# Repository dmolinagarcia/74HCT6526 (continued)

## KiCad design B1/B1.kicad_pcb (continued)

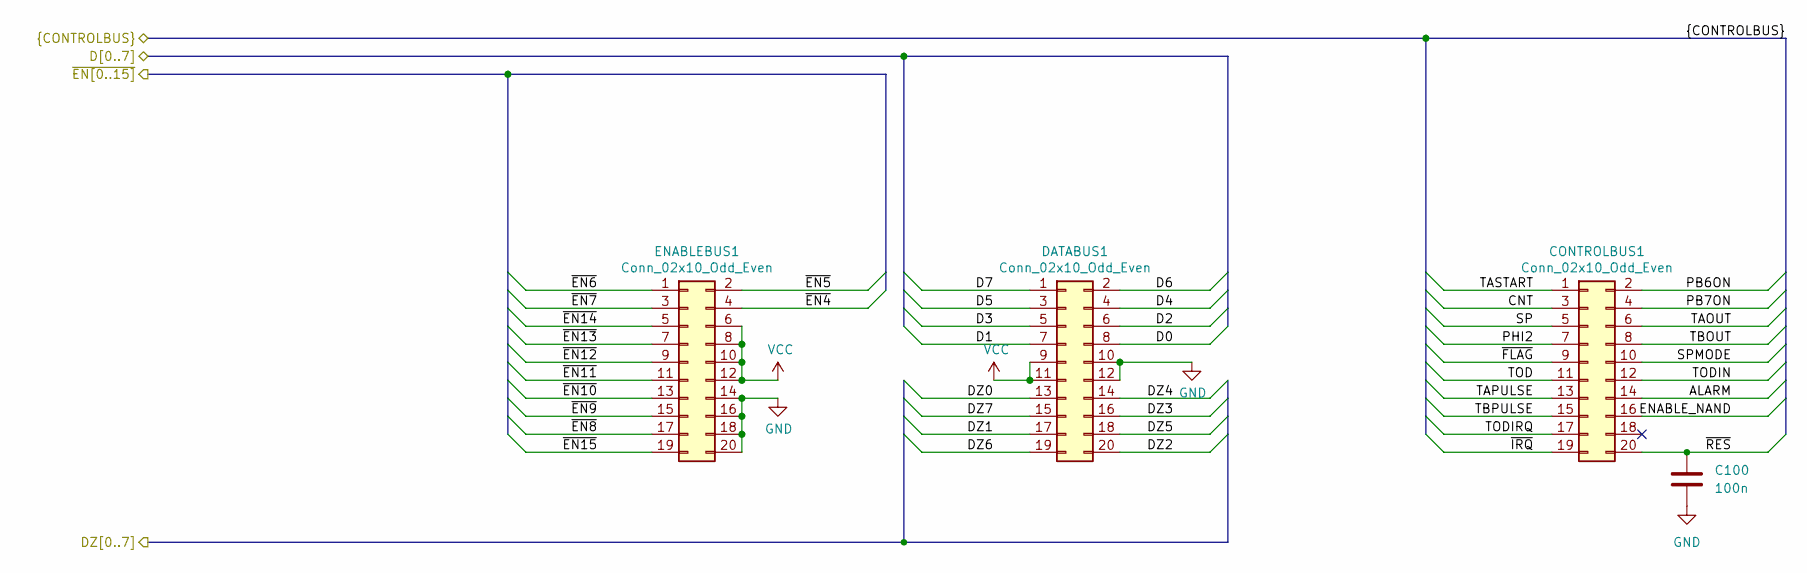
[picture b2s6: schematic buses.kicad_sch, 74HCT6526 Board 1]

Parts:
C100: 100n; C_0603_1608Metric
CONTROLBUS1: Conn_02x10_Odd_Even; PinHeader_2x10_P2.54mm_Vertical
DATABUS1: Conn_02x10_Odd_Even; PinHeader_2x10_P2.54mm_Vertical
ENABLEBUS1: Conn_02x10_Odd_Even; PinHeader_2x10_P2.54mm_Vertical

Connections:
ALARM: CONTROLBUS1.14
CNT: CONTROLBUS1.3; also elsewhere on the board
D0: DATABUS1.8; also elsewhere on the board
D1: DATABUS1.7; also elsewhere on the board
D2: DATABUS1.6; also elsewhere on the board
D3: DATABUS1.5; also elsewhere on the board
D4: DATABUS1.4; also elsewhere on the board
D5: DATABUS1.3; also elsewhere on the board
D6: DATABUS1.2; also elsewhere on the board
D7: DATABUS1.1; also elsewhere on the board
DZ0: DATABUS1.13; also elsewhere on the board
DZ1: DATABUS1.17; also elsewhere on the board
DZ2: DATABUS1.20; also elsewhere on the board
DZ3: DATABUS1.16; also elsewhere on the board
DZ4: DATABUS1.14; also elsewhere on the board
DZ5: DATABUS1.18; also elsewhere on the board
DZ6: DATABUS1.19; also elsewhere on the board
DZ7: DATABUS1.15; also elsewhere on the board
ENABLE_NAND: CONTROLBUS1.16; also elsewhere on the board
GND: C100.2, DATABUS1.10, DATABUS1.12, ENABLEBUS1.14, ENABLEBUS1.16, ENABLEBUS1.18, ENABLEBUS1.20; also elsewhere on the board
PB6ON: CONTROLBUS1.2; also elsewhere on the board
PB7ON: CONTROLBUS1.4
PHI2: CONTROLBUS1.7; also elsewhere on the board
SP: CONTROLBUS1.5
SPMODE: CONTROLBUS1.10; also elsewhere on the board
TAOUT: CONTROLBUS1.6; also elsewhere on the board
TAPULSE: CONTROLBUS1.13; also elsewhere on the board
TASTART: CONTROLBUS1.1; also elsewhere on the board
TBOUT: CONTROLBUS1.8
TBPULSE: CONTROLBUS1.15
TOD: CONTROLBUS1.11
TODIN: CONTROLBUS1.12; also elsewhere on the board
TODIRQ: CONTROLBUS1.17
VCC: DATABUS1.9, DATABUS1.11, ENABLEBUS1.6, ENABLEBUS1.8, ENABLEBUS1.10, ENABLEBUS1.12; also elsewhere on the board
~EN4: ENABLEBUS1.4; also elsewhere on the board
~EN5: ENABLEBUS1.2; also elsewhere on the board
~EN6: ENABLEBUS1.1
~EN7: ENABLEBUS1.3
~EN8: ENABLEBUS1.17
~EN9: ENABLEBUS1.15
~EN10: ENABLEBUS1.13
~EN11: ENABLEBUS1.11
~EN12: ENABLEBUS1.9
~EN13: ENABLEBUS1.7
~EN14: ENABLEBUS1.5; also elsewhere on the board
~EN15: ENABLEBUS1.19
~FLAG: CONTROLBUS1.9
~IRQ: CONTROLBUS1.19
~RES: C100.1, CONTROLBUS1.20; also elsewhere on the board

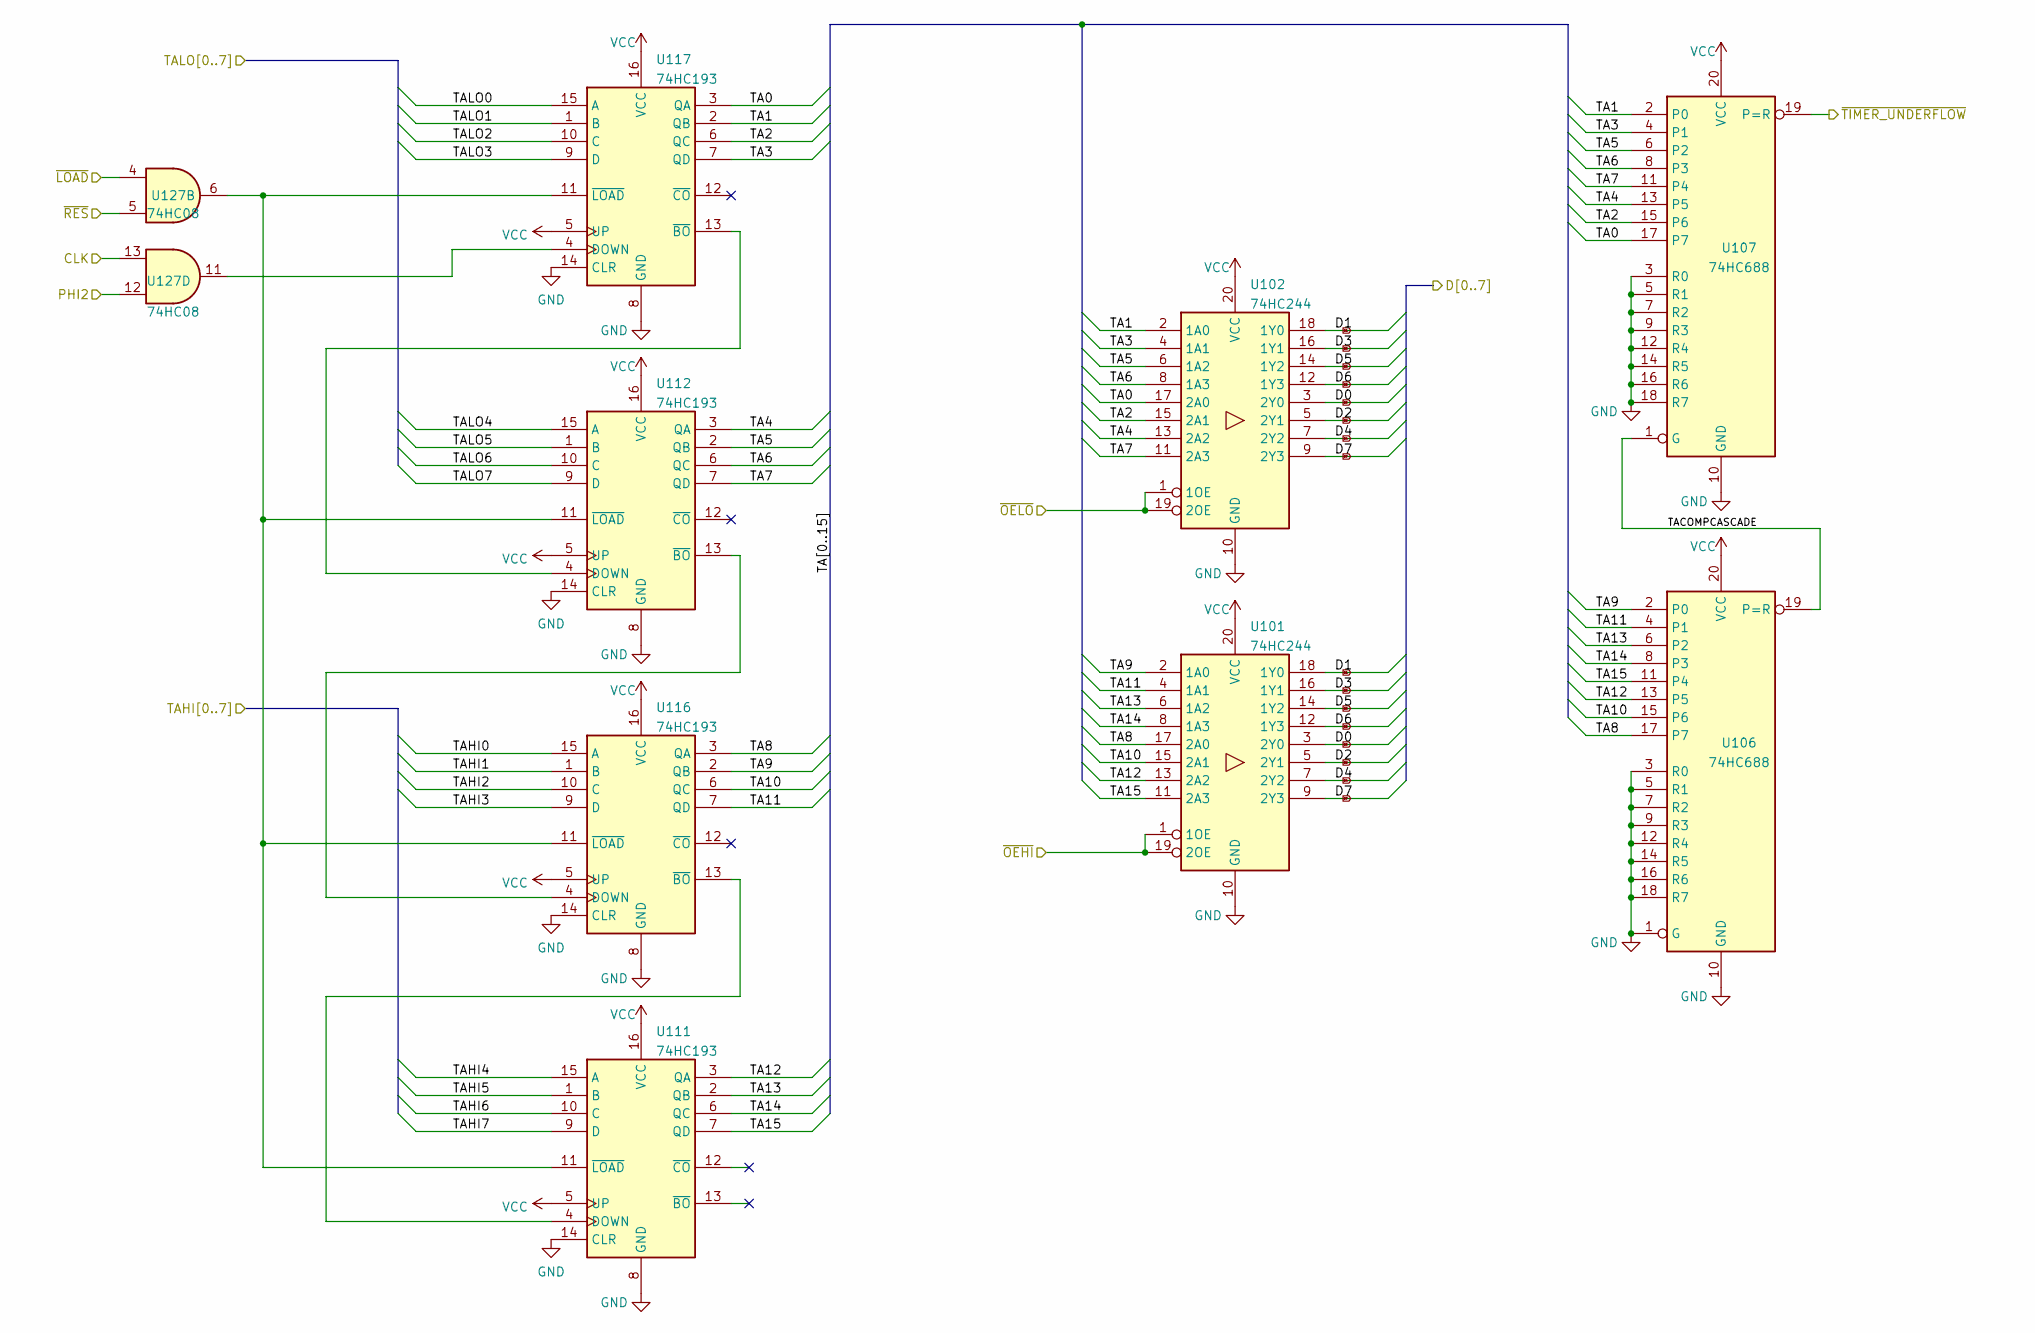
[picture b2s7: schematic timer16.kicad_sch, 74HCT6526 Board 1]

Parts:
U101, U102: 74HC244; SOIC-20W_7.5x12.8mm_P1.27mm
U106, U107: 74HC688; SOIC-20W_7.5x12.8mm_P1.27mm
U111, U112, U116, U117: 74HC193; SOIC-16_3.9x9.9mm_P1.27mm
U127: 74HC08; SO-14_3.9x8.65mm_P1.27mm

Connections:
/timera/TACOUNT: U127.13; also elsewhere on the board
/timera/timer16/TA0: U102.17 (2A0), U107.17 (P7), U117.3 (QA)
/timera/timer16/TA1: U102.2 (1A0), U107.2 (P0), U117.2 (QB)
/timera/timer16/TA2: U102.15 (2A1), U107.15 (P6), U117.6 (QC)
/timera/timer16/TA3: U102.4 (1A1), U107.4 (P1), U117.7 (QD)
/timera/timer16/TA4: U102.13 (2A2), U107.13 (P5), U112.3 (QA)
/timera/timer16/TA5: U102.6 (1A2), U107.6 (P2), U112.2 (QB)
/timera/timer16/TA6: U102.8 (1A3), U107.8 (P3), U112.6 (QC)
/timera/timer16/TA7: U102.11 (2A3), U107.11 (P4), U112.7 (QD)
/timera/timer16/TA8: U101.17 (2A0), U106.17 (P7), U116.3 (QA)
/timera/timer16/TA9: U101.2 (1A0), U106.2 (P0), U116.2 (QB)
/timera/timer16/TA10: U101.15 (2A1), U106.15 (P6), U116.6 (QC)
/timera/timer16/TA11: U101.4 (1A1), U106.4 (P1), U116.7 (QD)
/timera/timer16/TA12: U101.13 (2A2), U106.13 (P5), U111.3 (QA)
/timera/timer16/TA13: U101.6 (1A2), U106.6 (P2), U111.2 (QB)
/timera/timer16/TA14: U101.8 (1A3), U106.8 (P3), U111.6 (QC)
/timera/timer16/TA15: U101.11 (2A3), U106.11 (P4), U111.7 (QD)
/timera/timer16/TACOMPCASCADE: U106.19 (P=R), U107.1 (G)
/timera/timer16/TAHI0: U116.15 (A); also elsewhere on the board
/timera/timer16/TAHI1: U116.1 (B); also elsewhere on the board
/timera/timer16/TAHI2: U116.10 (C); also elsewhere on the board
/timera/timer16/TAHI3: U116.9 (D); also elsewhere on the board
/timera/timer16/TAHI4: U111.15 (A); also elsewhere on the board
/timera/timer16/TAHI5: U111.1 (B); also elsewhere on the board
/timera/timer16/TAHI6: U111.10 (C); also elsewhere on the board
/timera/timer16/TAHI7: U111.9 (D); also elsewhere on the board
/timera/timer16/TALO0: U117.15 (A); also elsewhere on the board
/timera/timer16/TALO1: U117.1 (B); also elsewhere on the board
/timera/timer16/TALO2: U117.10 (C); also elsewhere on the board
/timera/timer16/TALO3: U117.9 (D); also elsewhere on the board
/timera/timer16/TALO4: U112.15 (A); also elsewhere on the board
/timera/timer16/TALO5: U112.1 (B); also elsewhere on the board
/timera/timer16/TALO6: U112.10 (C); also elsewhere on the board
/timera/timer16/TALO7: U112.9 (D); also elsewhere on the board
/timera/timer16/~TIMER_UNDERFLOW: U107.19 (P=R); also elsewhere on the board
/timera/~OETAHI: U101.1 (1OE), U101.19 (2OE); also elsewhere on the board
/timera/~OETALO: U102.1 (1OE), U102.19 (2OE); also elsewhere on the board
/timera/~TALOAD: U127.4; also elsewhere on the board
D0: U101.3 (2Y0), U102.3 (2Y0); also elsewhere on the board
D1: U101.18 (1Y0), U102.18 (1Y0); also elsewhere on the board
D2: U101.5 (2Y1), U102.5 (2Y1); also elsewhere on the board
D3: U101.16 (1Y1), U102.16 (1Y1); also elsewhere on the board
D4: U101.7 (2Y2), U102.7 (2Y2); also elsewhere on the board
D5: U101.14 (1Y2), U102.14 (1Y2); also elsewhere on the board
D6: U101.12 (1Y3), U102.12 (1Y3); also elsewhere on the board
D7: U101.9 (2Y3), U102.9 (2Y3); also elsewhere on the board
GND: U101.10 (GND), U102.10 (GND), U106.1 (G), U106.3 (R0), U106.5 (R1), U106.7 (R2), U106.9 (R3), U106.10 (GND), U106.12 (R4), U106.14 (R5), U106.16 (R6), U106.18 (R7), U107.3 (R0), U107.5 (R1), U107.7 (R2), U107.9 (R3), U107.10 (GND), U107.12 (R4), U107.14 (R5), U107.16 (R6), U107.18 (R7), U111.8 (GND), U111.14 (CLR), U112.8 (GND), U112.14 (CLR), U116.8 (GND), U116.14 (CLR), U117.8 (GND), U117.14 (CLR); also elsewhere on the board
unnamed: U111.4 (DOWN), U116.13 (~BO)
unnamed: U111.11 (~LOAD), U112.11 (~LOAD), U116.11 (~LOAD), U117.11 (~LOAD), U127.6
unnamed: U112.4 (DOWN), U117.13 (~BO)
unnamed: U112.13 (~BO), U116.4 (DOWN)
unnamed: U117.4 (DOWN), U127.11
PHI2: U127.12; also elsewhere on the board
VCC: U101.20 (VCC), U102.20 (VCC), U106.20 (VCC), U107.20 (VCC), U111.5 (UP), U111.16 (VCC), U112.5 (UP), U112.16 (VCC), U116.5 (UP), U116.16 (VCC), U117.5 (UP), U117.16 (VCC); also elsewhere on the board
~RES: U127.5; also elsewhere on the board

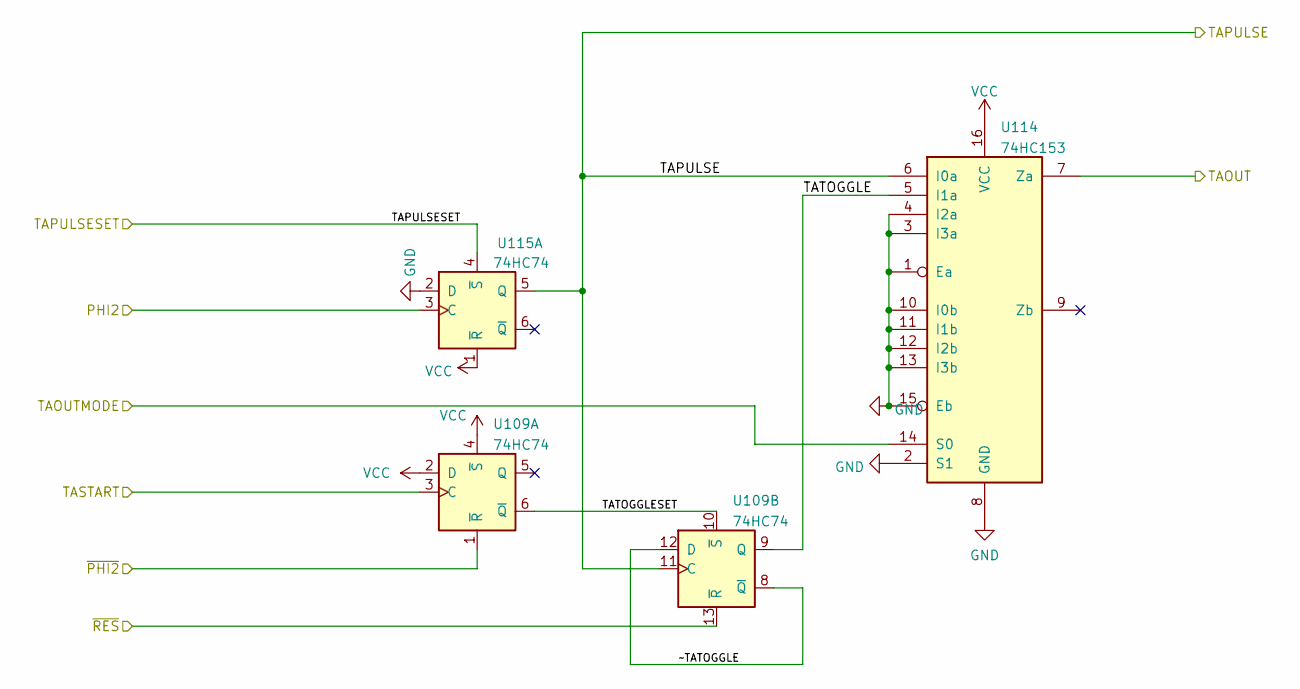
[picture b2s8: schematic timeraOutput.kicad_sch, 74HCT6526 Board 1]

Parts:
U109, U115: 74HC74; SO-14_3.9x8.65mm_P1.27mm
U114: 74HC153; SOIC-16_3.9x9.9mm_P1.27mm

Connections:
/TAOUTMODE: U114.14 (S0); also elsewhere on the board
/timera/timeraOutput/TAPULSESET: U115.4 (~S); also elsewhere on the board
/timera/timeraOutput/TATOGGLE: U109.9 (Q), U114.5 (I1a)
/timera/timeraOutput/TATOGGLESET: U109.6 (~Q), U109.10 (~S)
/timera/timeraOutput/~TATOGGLE: U109.8 (~Q), U109.12 (D)
/~PHI2: U109.1 (~R); also elsewhere on the board
GND: U114.1 (Ea), U114.2 (S1), U114.3 (I3a), U114.4 (I2a), U114.8 (GND), U114.10 (I0b), U114.11 (I1b), U114.12 (I2b), U114.13 (I3b), U114.15 (Eb), U115.2 (D); also elsewhere on the board
PHI2: U115.3 (C); also elsewhere on the board
TAOUT: U114.7 (Za); also elsewhere on the board
TAPULSE: U109.11 (C), U114.6 (I0a), U115.5 (Q); also elsewhere on the board
TASTART: U109.3 (C); also elsewhere on the board
VCC: U109.2 (D), U109.4 (~S), U114.16 (VCC), U115.1 (~R); also elsewhere on the board
~RES: U109.13 (~R); also elsewhere on the board

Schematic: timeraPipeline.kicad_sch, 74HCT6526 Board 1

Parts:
U110: 74HC04; SOIC-14_3.9x8.7mm_P1.27mm
U113: 74HC27; SO-14_3.9x8.65mm_P1.27mm
U118, U119, U129: 74HC74; SO-14_3.9x8.65mm_P1.27mm
U127: 74HC08; SO-14_3.9x8.65mm_P1.27mm

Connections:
/TALOAD: U113.10; also elsewhere on the board
/crega/TAUNDERFLOW: U110.13, U113.6, U113.9; also elsewhere on the board
/timera/TACOUNT: U119.5 (Q); also elsewhere on the board
/timera/timer16/~TIMER_UNDERFLOW: U113.3; also elsewhere on the board
/timera/timeraOutput/TAPULSESET: U110.12, U118.13 (~R); also elsewhere on the board
/timera/timeraPipeline/TIMERAINPUT: U127.10; also elsewhere on the board
/timera/~TALOAD: U129.9 (Q); also elsewhere on the board
/timera/~WETAHI: U113.13; also elsewhere on the board
/~PHI2: U129.3 (C), U129.11 (C); also elsewhere on the board
GND: U113.2, U113.4; also elsewhere on the board
unnamed: U113.5, U118.8 (~Q)
unnamed: U113.8, U129.1 (~R), U129.13 (~R)
unnamed: U113.11, U113.12
unnamed: U118.9 (Q), U119.1 (~R), U119.2 (D)
unnamed: U118.12 (D), U127.8
unnamed: U129.5 (Q), U129.12 (D)
PHI2: U118.11 (C), U119.3 (C); also elsewhere on the board
TASTART: U113.1, U127.9; also elsewhere on the board
VCC: U118.10 (~S), U119.4 (~S), U129.2 (D), U129.4 (~S), U129.10 (~S); also elsewhere on the board

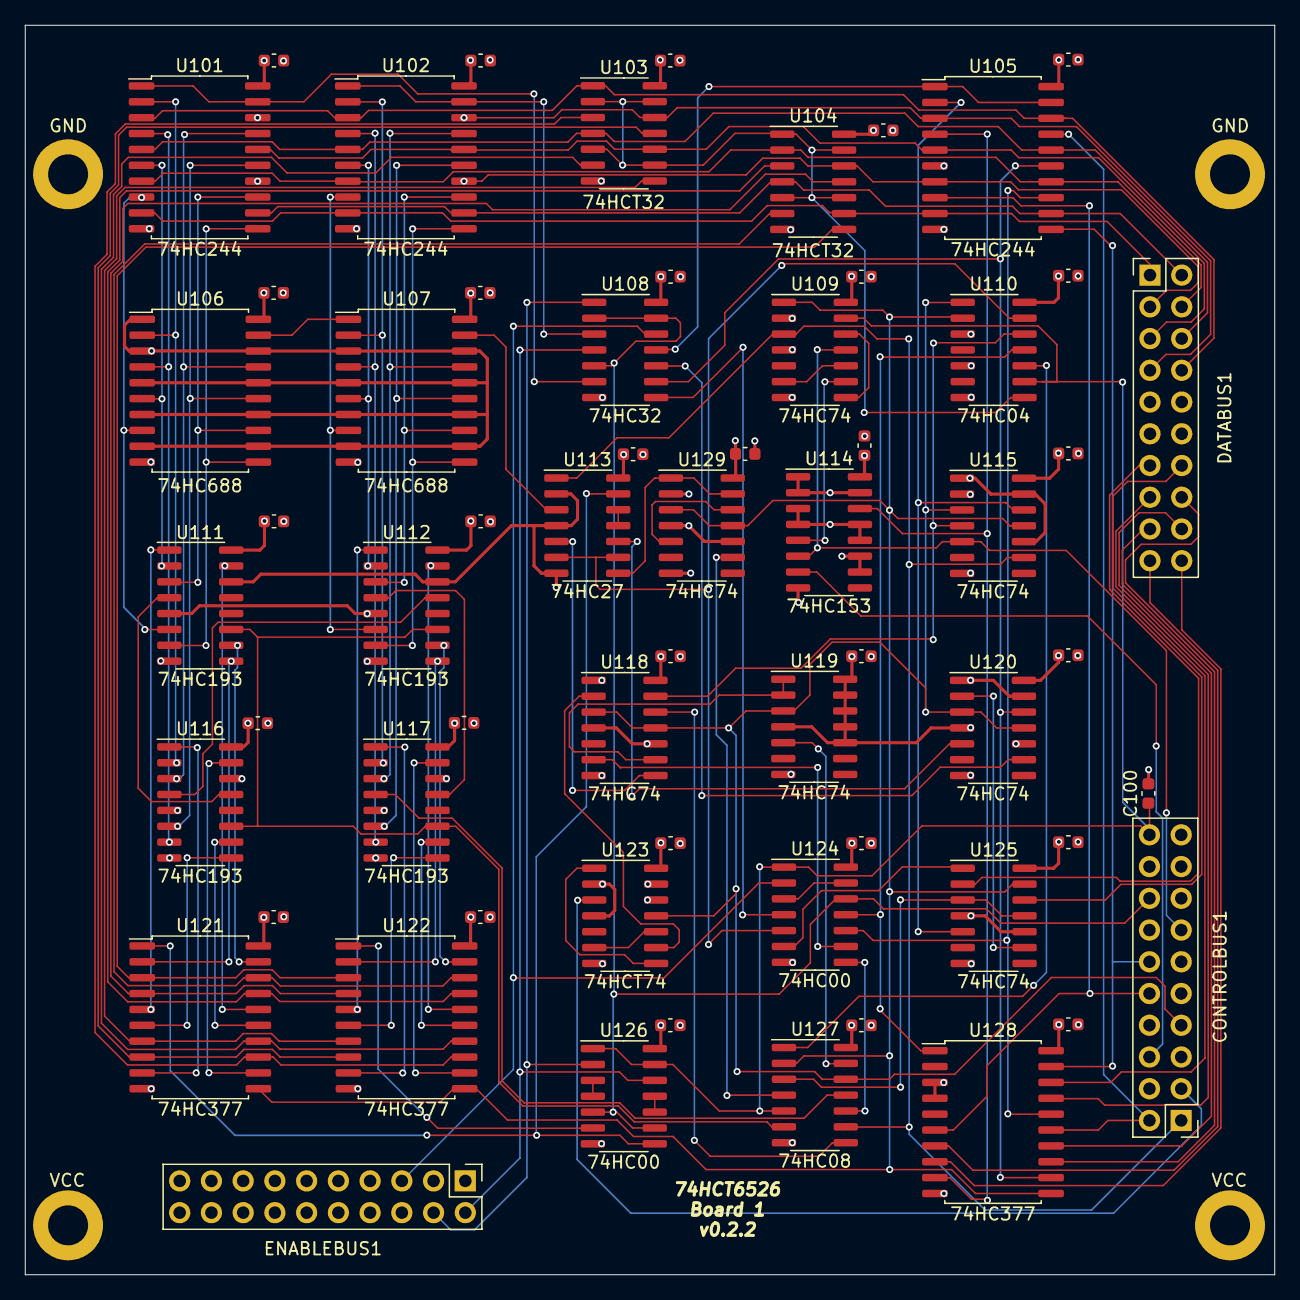
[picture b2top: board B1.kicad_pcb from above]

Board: 4 copper layers, 100.0 x 100.0 mm, 66 parts (0 on the bottom side), 118 nets.

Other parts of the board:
GND101, GND102: GND; MountingHole_2.2mm_M2_DIN965_Pad
VCC101, VCC102: VCC; MountingHole_2.2mm_M2_DIN965_Pad

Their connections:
GND: GND101.GND, GND102.GND; also elsewhere on the board
VCC: VCC101.VCC, VCC102.VCC; also elsewhere on the board

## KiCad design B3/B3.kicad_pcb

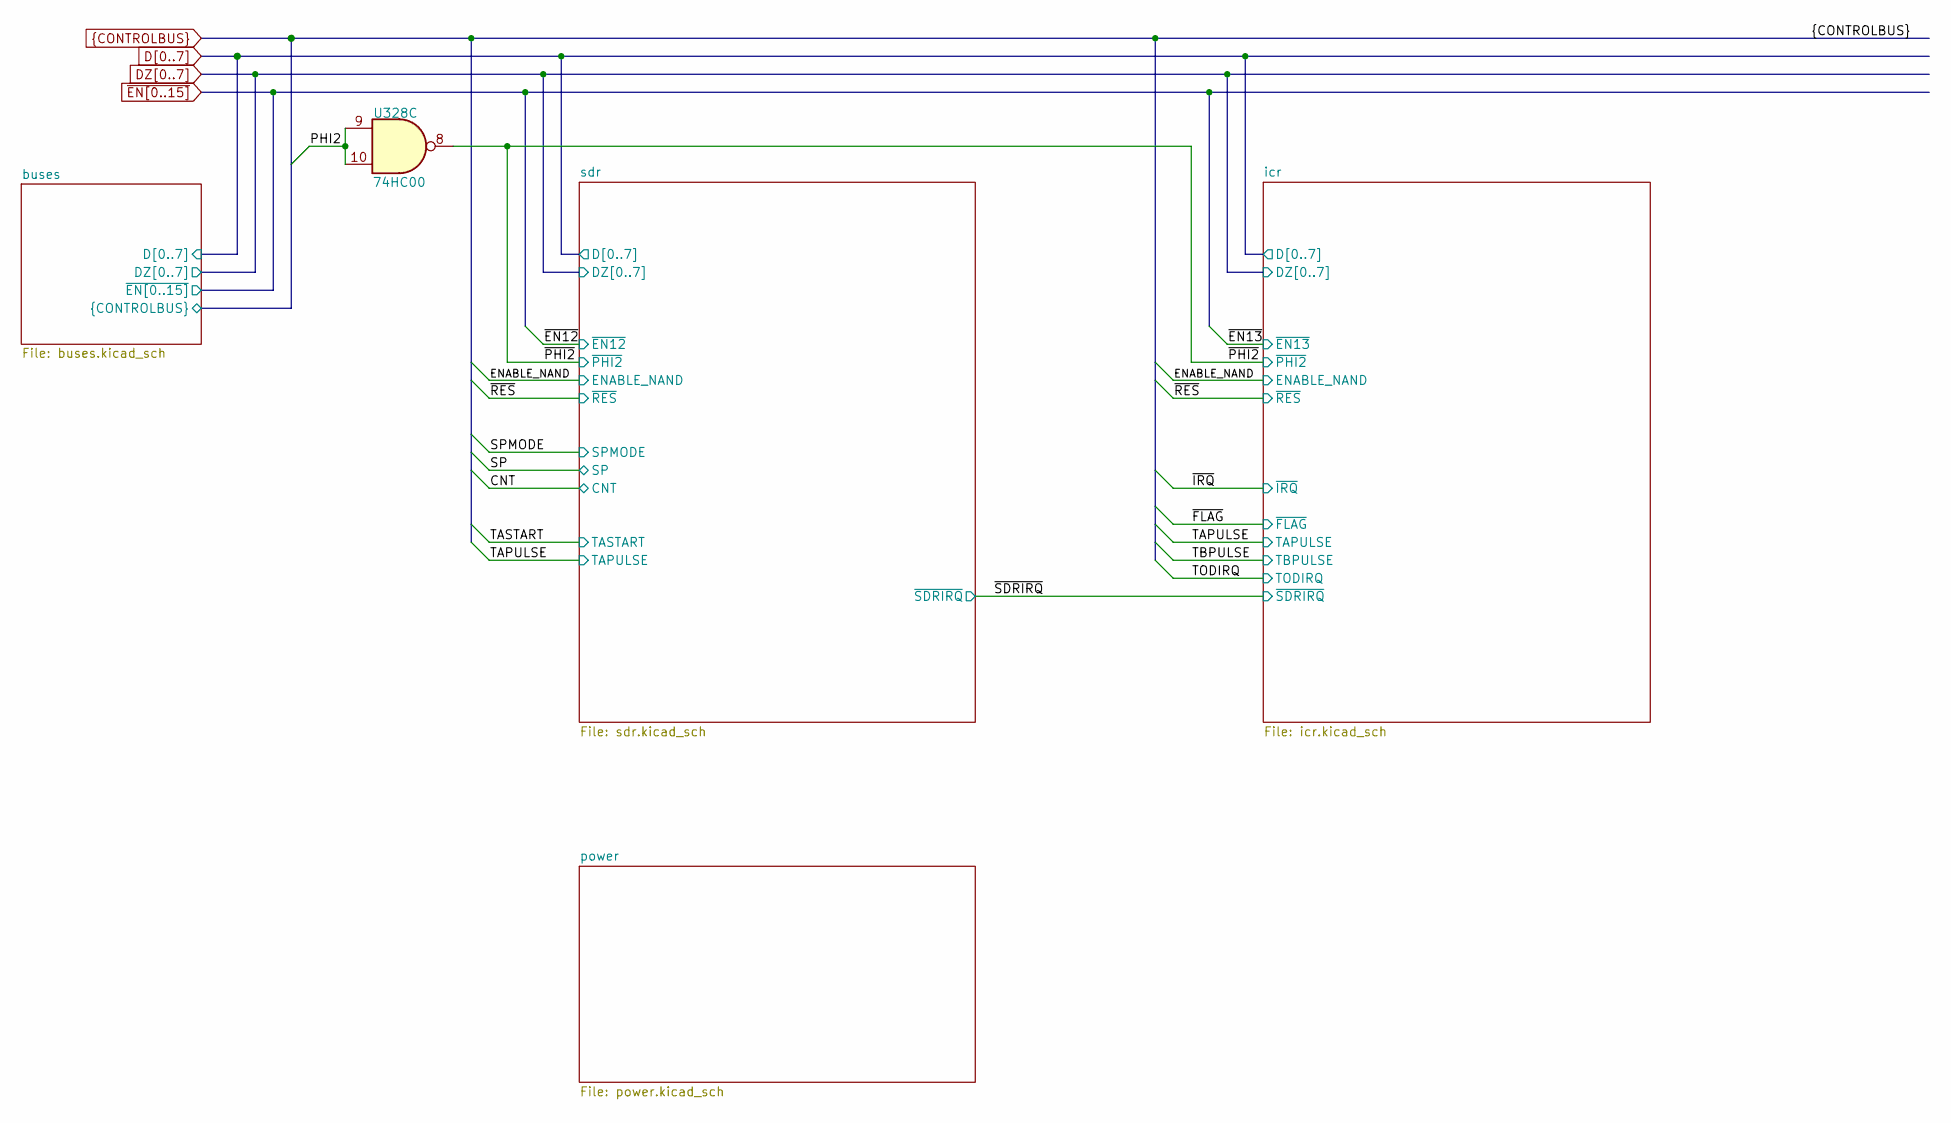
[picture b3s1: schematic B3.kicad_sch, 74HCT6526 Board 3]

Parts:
U328: 74HC00; SO-14_3.9x8.65mm_P1.27mm

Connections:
/~PHI2: U328.8; also elsewhere on the board
PHI2: U328.9, U328.10; also elsewhere on the board

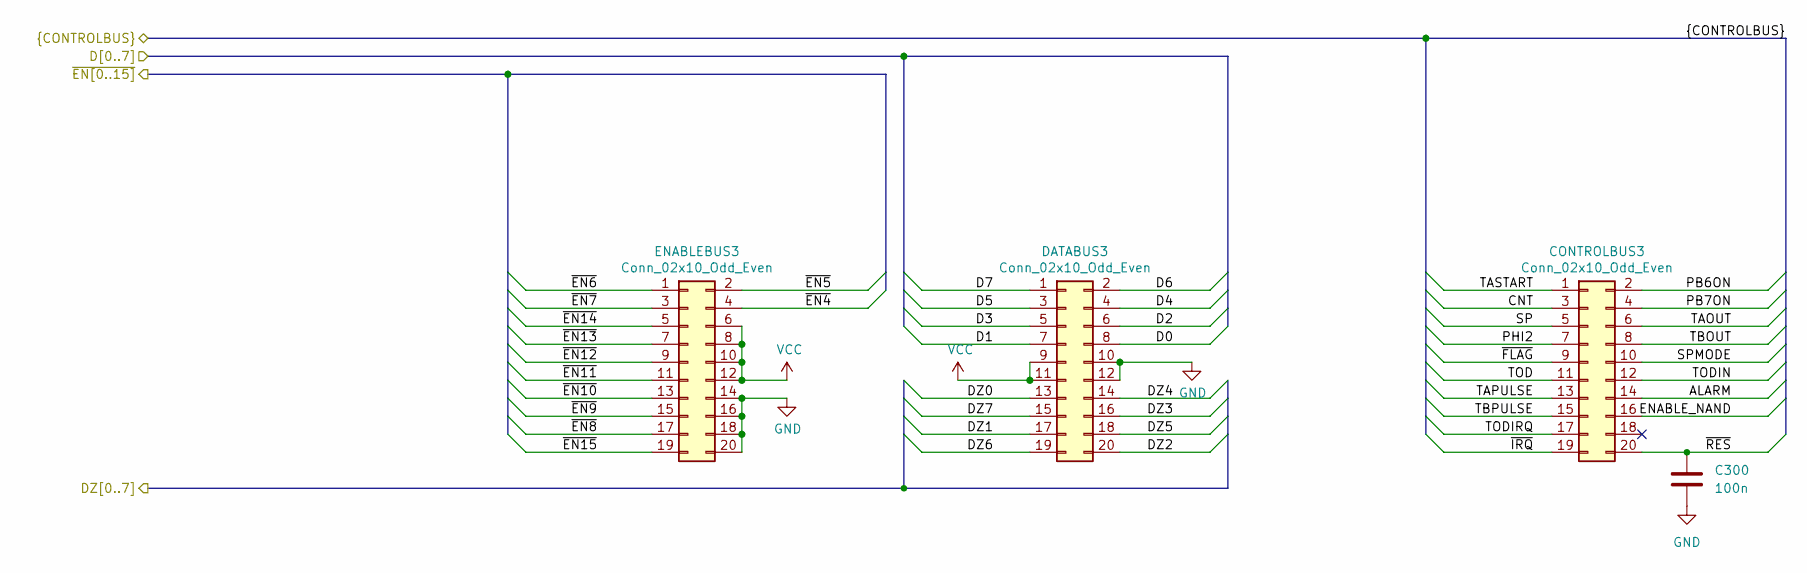
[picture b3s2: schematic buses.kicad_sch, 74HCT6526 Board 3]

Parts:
C300: 100n; C_0603_1608Metric
CONTROLBUS3: Conn_02x10_Odd_Even; PinHeader_2x10_P2.54mm_Vertical
DATABUS3: Conn_02x10_Odd_Even; PinHeader_2x10_P2.54mm_Vertical
ENABLEBUS3: Conn_02x10_Odd_Even; PinHeader_2x10_P2.54mm_Vertical

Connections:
ALARM: CONTROLBUS3.14
CNT: CONTROLBUS3.3; also elsewhere on the board
D0: DATABUS3.8; also elsewhere on the board
D1: DATABUS3.7; also elsewhere on the board
D2: DATABUS3.6; also elsewhere on the board
D3: DATABUS3.5; also elsewhere on the board
D4: DATABUS3.4; also elsewhere on the board
D5: DATABUS3.3; also elsewhere on the board
D6: DATABUS3.2; also elsewhere on the board
D7: DATABUS3.1; also elsewhere on the board
DZ0: DATABUS3.13; also elsewhere on the board
DZ1: DATABUS3.17; also elsewhere on the board
DZ2: DATABUS3.20; also elsewhere on the board
DZ3: DATABUS3.16; also elsewhere on the board
DZ4: DATABUS3.14; also elsewhere on the board
DZ5: DATABUS3.18; also elsewhere on the board
DZ6: DATABUS3.19; also elsewhere on the board
DZ7: DATABUS3.15; also elsewhere on the board
ENABLE_NAND: CONTROLBUS3.16; also elsewhere on the board
GND: C300.2, DATABUS3.10, DATABUS3.12, ENABLEBUS3.14, ENABLEBUS3.16, ENABLEBUS3.18, ENABLEBUS3.20; also elsewhere on the board
PB6ON: CONTROLBUS3.2
PB7ON: CONTROLBUS3.4
PHI2: CONTROLBUS3.7; also elsewhere on the board
SP: CONTROLBUS3.5; also elsewhere on the board
SPMODE: CONTROLBUS3.10; also elsewhere on the board
TAOUT: CONTROLBUS3.6
TAPULSE: CONTROLBUS3.13; also elsewhere on the board
TASTART: CONTROLBUS3.1; also elsewhere on the board
TBOUT: CONTROLBUS3.8
TBPULSE: CONTROLBUS3.15; also elsewhere on the board
TOD: CONTROLBUS3.11
TODIN: CONTROLBUS3.12
TODIRQ: CONTROLBUS3.17; also elsewhere on the board
VCC: DATABUS3.9, DATABUS3.11, ENABLEBUS3.6, ENABLEBUS3.8, ENABLEBUS3.10, ENABLEBUS3.12; also elsewhere on the board
~EN4: ENABLEBUS3.4
~EN5: ENABLEBUS3.2
~EN6: ENABLEBUS3.1
~EN7: ENABLEBUS3.3
~EN8: ENABLEBUS3.17
~EN9: ENABLEBUS3.15
~EN10: ENABLEBUS3.13
~EN11: ENABLEBUS3.11
~EN12: ENABLEBUS3.9; also elsewhere on the board
~EN13: ENABLEBUS3.7; also elsewhere on the board
~EN14: ENABLEBUS3.5
~EN15: ENABLEBUS3.19
~FLAG: CONTROLBUS3.9; also elsewhere on the board
~IRQ: CONTROLBUS3.19; also elsewhere on the board
~RES: C300.1, CONTROLBUS3.20; also elsewhere on the board

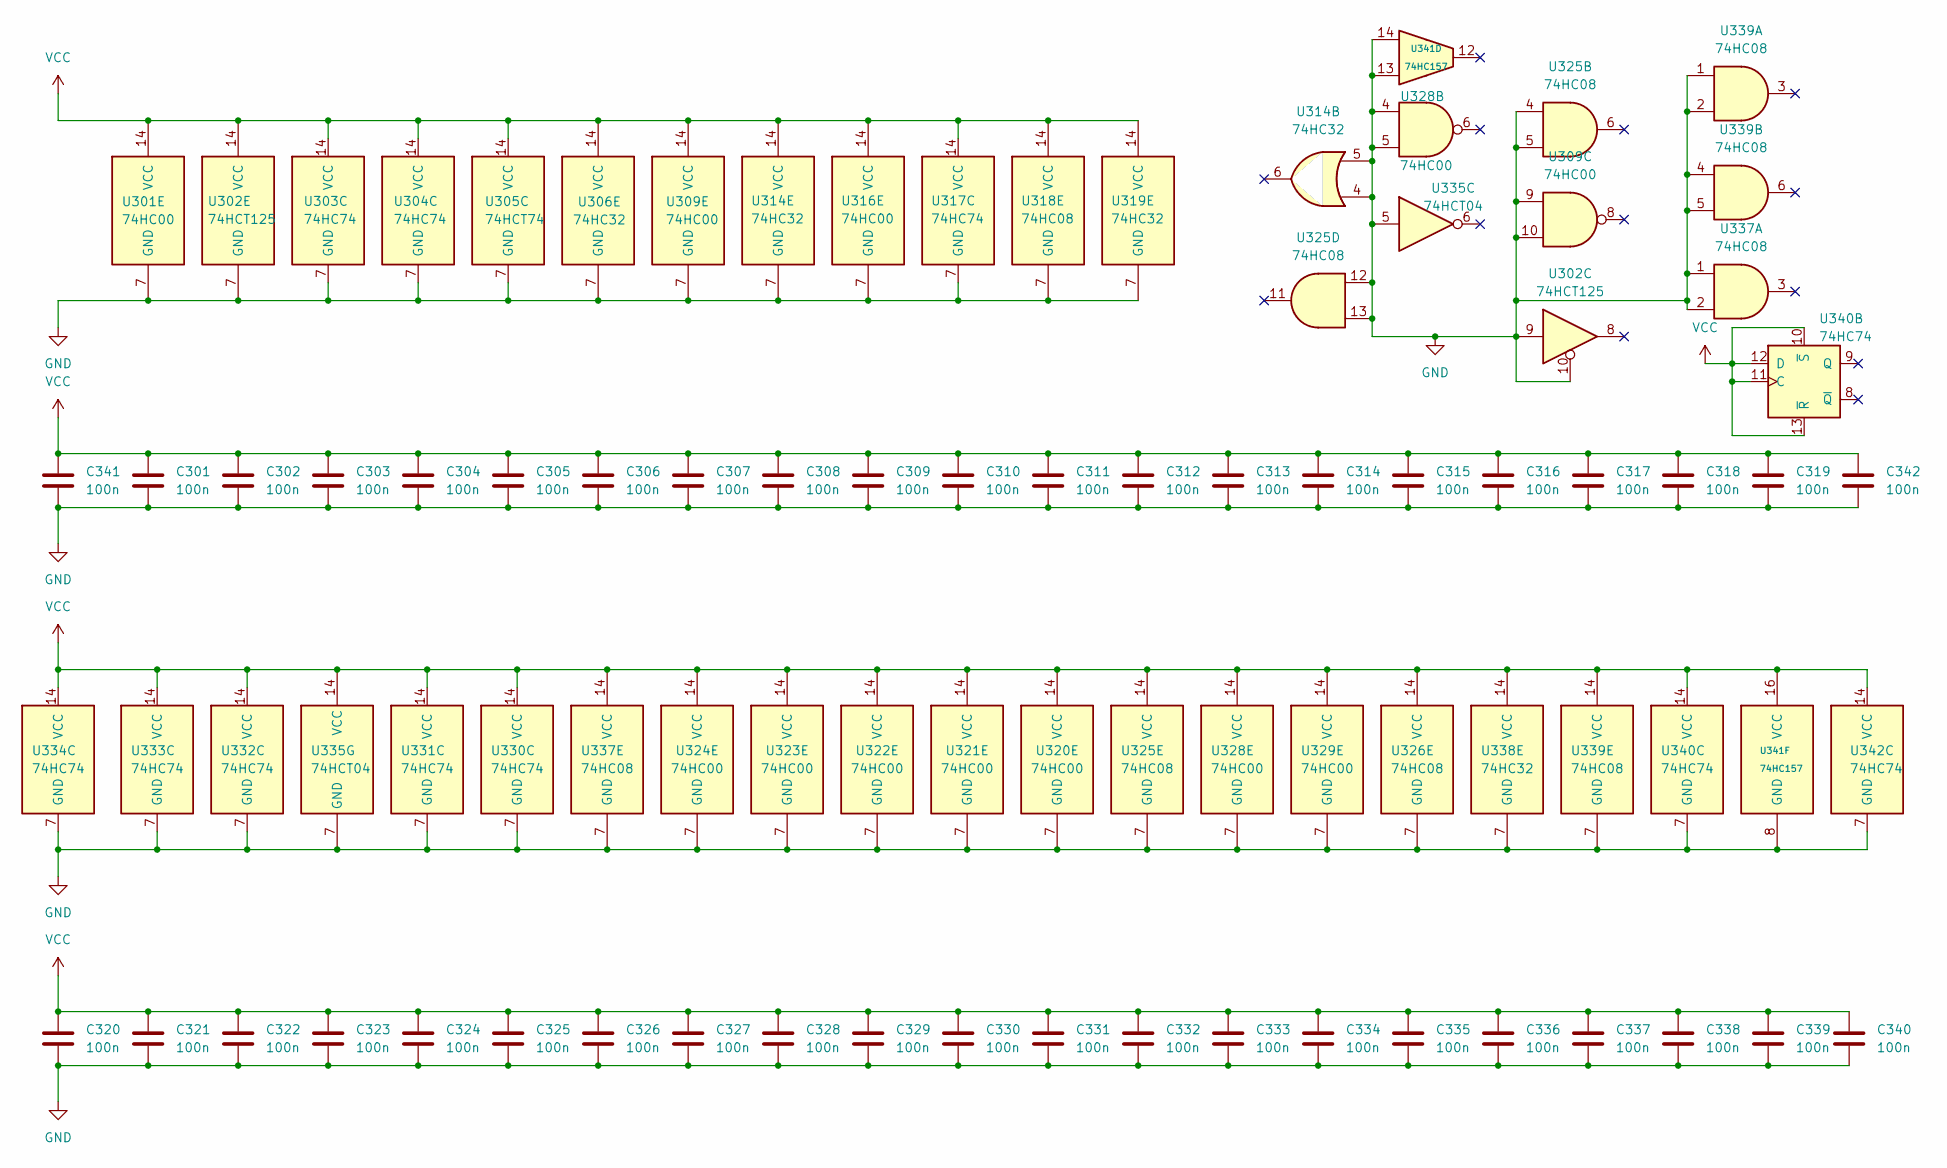
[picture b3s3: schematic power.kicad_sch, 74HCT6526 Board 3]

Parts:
C301, C302, C303, C304, C305, C306, C307, C308, C309, C310, C311, C312, C313, C314, C315, C316, C317, C318, C319, C320, C321, C322, C323, C324, C325, C326, C327, C328, C329, C330, C331, C332, C333, C334, C335, C336, C337, C338, C339, C340, C341, C342: 100n; C_0603_1608Metric
U301, U309, U316, U320, U321, U322, U323, U324, U328, U329: 74HC00; SO-14_3.9x8.65mm_P1.27mm
U302: 74HCT125; SO-14_3.9x8.65mm_P1.27mm
U303, U304, U317, U330, U331, U332, U333, U334, U340, U342: 74HC74; SO-14_3.9x8.65mm_P1.27mm
U305: 74HCT74; SO-14_3.9x8.65mm_P1.27mm
U306, U314, U319, U338: 74HC32; SO-14_3.9x8.65mm_P1.27mm
U318, U325, U326, U337, U339: 74HC08; SO-14_3.9x8.65mm_P1.27mm
U335: 74HCT04; SO-14_3.9x8.65mm_P1.27mm
U341: 74HC157; SO-16_3.9x9.9mm_P1.27mm

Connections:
GND: C301.2, C302.2, C303.2, C304.2, C305.2, C306.2, C307.2, C308.2, C309.2, C310.2, C311.2, C312.2, C313.2, C314.2, C315.2, C316.2, C317.2, C318.2, C319.2, C320.2, C321.2, C322.2, C323.2, C324.2, C325.2, C326.2, C327.2, C328.2, C329.2, C330.2, C331.2, C332.2, C333.2, C334.2, C335.2, C336.2, C337.2, C338.2, C339.2, C340.2, C341.2, C342.2, U301.7 (GND), U302.7 (GND), U302.9, U302.10, U303.7 (GND), U304.7 (GND), U305.7 (GND), U306.7 (GND), U309.7 (GND), U309.9, U309.10, U314.4, U314.5, U314.7 (GND), U316.7 (GND), U317.7 (GND), U318.7 (GND), U319.7 (GND), U320.7 (GND), U321.7 (GND), U322.7 (GND), U323.7 (GND), U324.7 (GND), U325.4, U325.5, U325.7 (GND), U325.12, U325.13, U326.7 (GND), U328.4, U328.5, U328.7 (GND), U329.7 (GND), U330.7 (GND), U331.7 (GND), U332.7 (GND), U333.7 (GND), U334.7 (GND), U335.5, U335.7 (GND), U337.1, U337.2, U337.7 (GND), U338.7 (GND), U339.1, U339.2, U339.4, U339.5, U339.7 (GND), U340.7 (GND), U341.8 (GND), U341.13, U341.14, U342.7 (GND); also elsewhere on the board
VCC: C301.1, C302.1, C303.1, C304.1, C305.1, C306.1, C307.1, C308.1, C309.1, C310.1, C311.1, C312.1, C313.1, C314.1, C315.1, C316.1, C317.1, C318.1, C319.1, C320.1, C321.1, C322.1, C323.1, C324.1, C325.1, C326.1, C327.1, C328.1, C329.1, C330.1, C331.1, C332.1, C333.1, C334.1, C335.1, C336.1, C337.1, C338.1, C339.1, C340.1, C341.1, C342.1, U301.14 (VCC), U302.14 (VCC), U303.14 (VCC), U304.14 (VCC), U305.14 (VCC), U306.14 (VCC), U309.14 (VCC), U314.14 (VCC), U316.14 (VCC), U317.14 (VCC), U318.14 (VCC), U319.14 (VCC), U320.14 (VCC), U321.14 (VCC), U322.14 (VCC), U323.14 (VCC), U324.14 (VCC), U325.14 (VCC), U326.14 (VCC), U328.14 (VCC), U329.14 (VCC), U330.14 (VCC), U331.14 (VCC), U332.14 (VCC), U333.14 (VCC), U334.14 (VCC), U335.14 (VCC), U337.14 (VCC), U338.14 (VCC), U339.14 (VCC), U340.10 (~S), U340.11 (C), U340.12 (D), U340.13 (~R), U340.14 (VCC), U341.16 (VCC), U342.14 (VCC); also elsewhere on the board

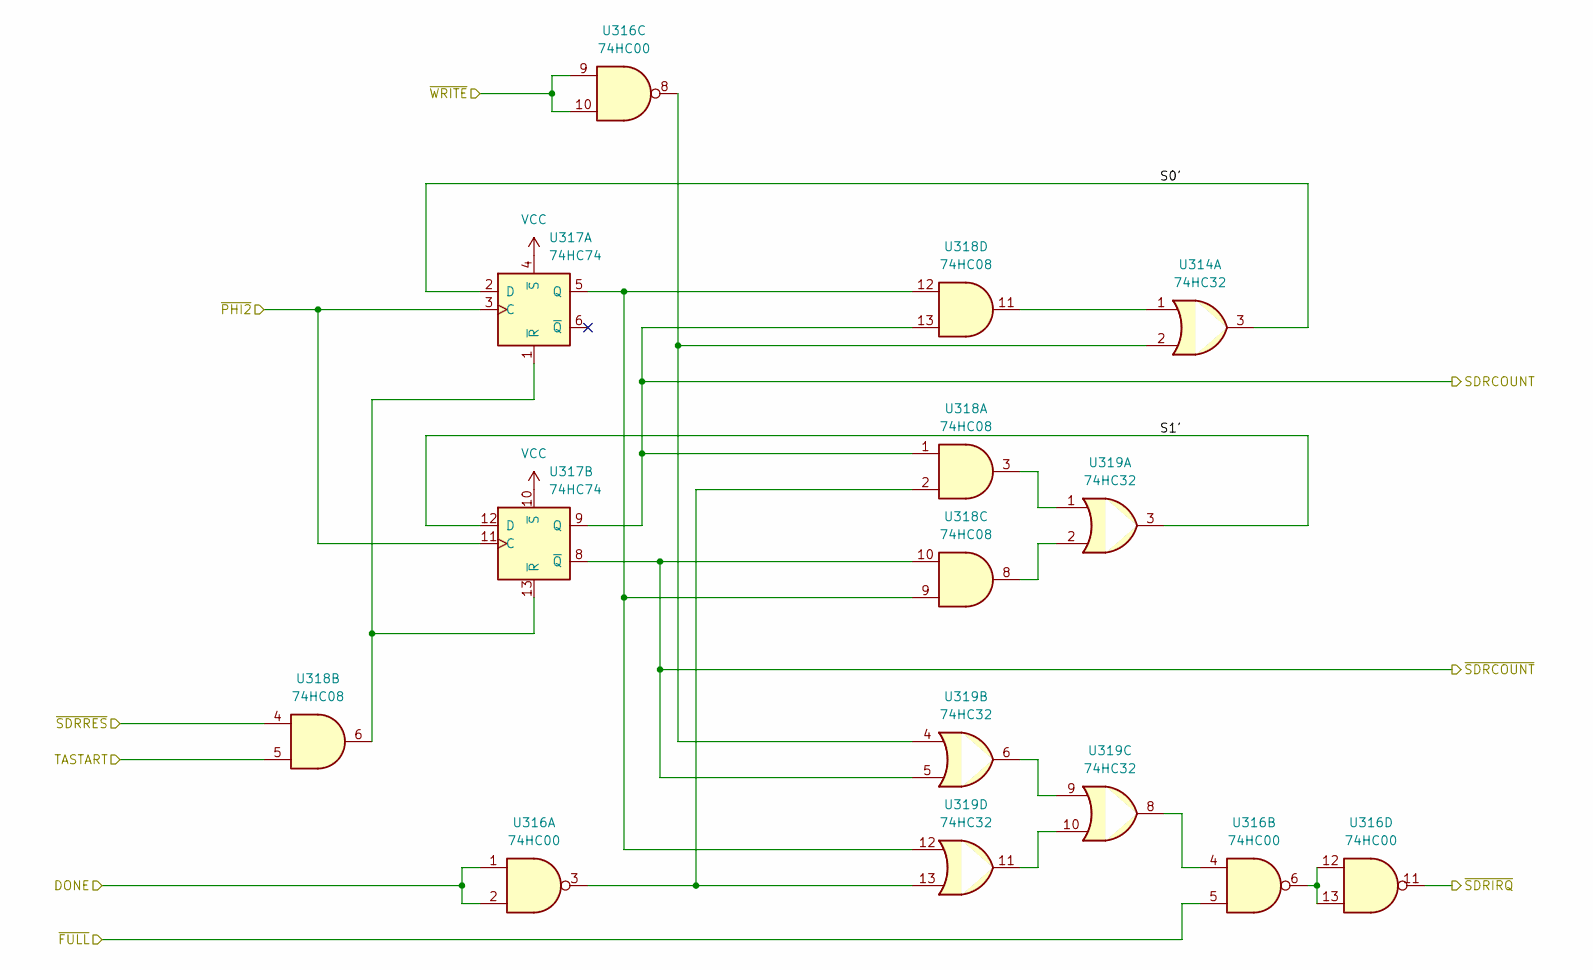
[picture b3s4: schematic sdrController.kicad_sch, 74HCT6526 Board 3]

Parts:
U314, U319: 74HC32; SO-14_3.9x8.65mm_P1.27mm
U316: 74HC00; SO-14_3.9x8.65mm_P1.27mm
U317: 74HC74; SO-14_3.9x8.65mm_P1.27mm
U318: 74HC08; SO-14_3.9x8.65mm_P1.27mm

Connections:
/sdr/sdrController/DONE: U316.1, U316.2; also elsewhere on the board
/sdr/sdrController/S0': U314.3, U317.2 (D)
/sdr/sdrController/S1': U317.12 (D), U319.3
/sdr/sdrController/SDRCOUNT: U317.9 (Q), U318.1, U318.13; also elsewhere on the board
/sdr/sdrController/~FULL: U316.5; also elsewhere on the board
/sdr/sdrController/~SDRCOUNT: U317.8 (~Q), U318.10, U319.5; also elsewhere on the board
/sdr/sdrController/~SDRRES: U318.4; also elsewhere on the board
/sdr/sdrController/~WRITE: U316.9, U316.10; also elsewhere on the board
/~PHI2: U317.3 (C), U317.11 (C); also elsewhere on the board
/~SDRIRQ: U316.11; also elsewhere on the board
unnamed: U314.1, U318.11
unnamed: U314.2, U316.8, U319.4
unnamed: U316.3, U318.2, U319.13
unnamed: U316.4, U319.8
unnamed: U316.6, U316.12, U316.13
unnamed: U317.1 (~R), U317.13 (~R), U318.6
unnamed: U317.5 (Q), U318.9, U318.12, U319.12
unnamed: U318.3, U319.1
unnamed: U318.8, U319.2
unnamed: U319.6, U319.9
unnamed: U319.10, U319.11
TASTART: U318.5; also elsewhere on the board
VCC: U317.4 (~S), U317.10 (~S); also elsewhere on the board
